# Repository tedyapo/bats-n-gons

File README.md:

# bats-n-gons
Nocturnal flying mammals, geometric shapes, and emergent behavior

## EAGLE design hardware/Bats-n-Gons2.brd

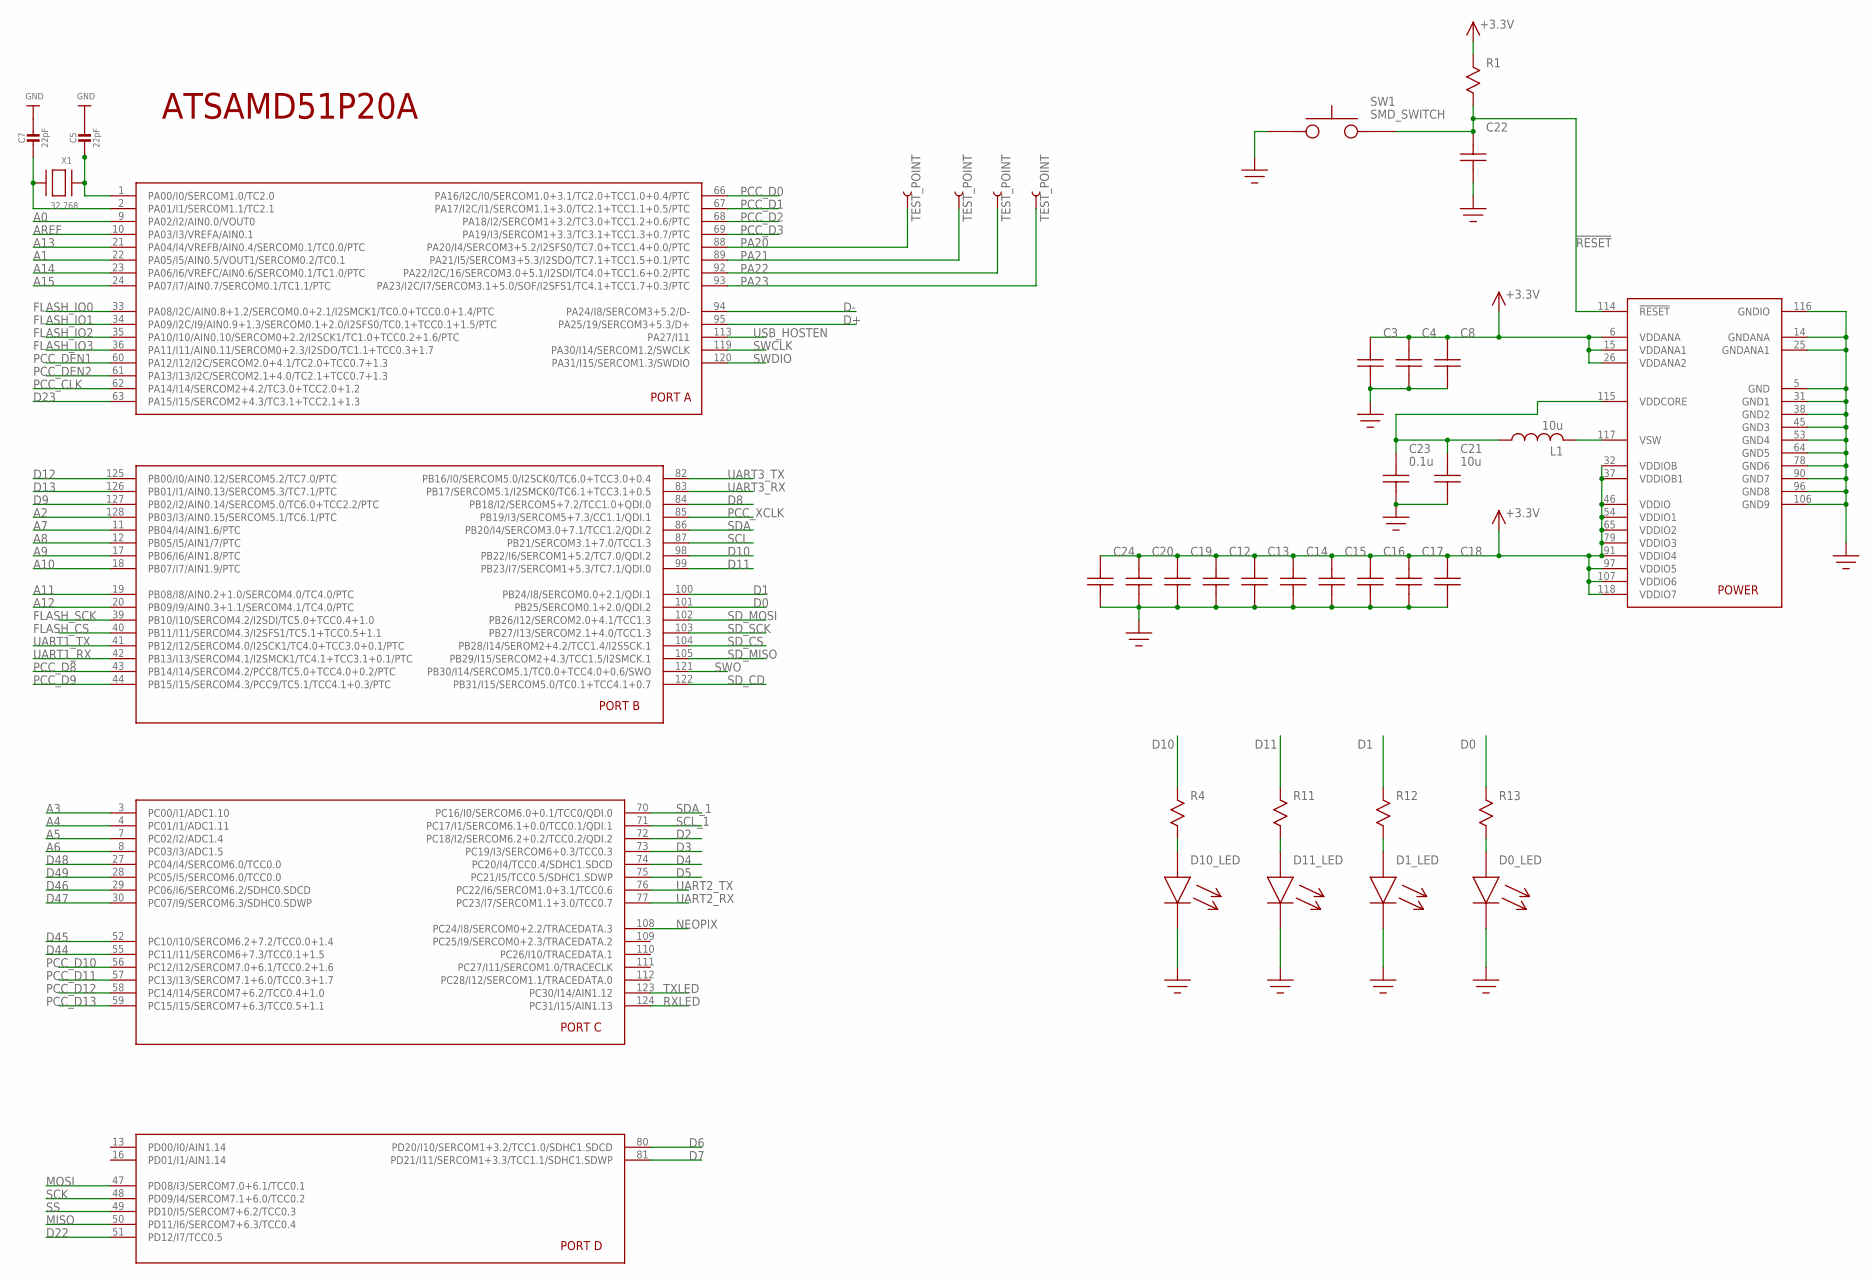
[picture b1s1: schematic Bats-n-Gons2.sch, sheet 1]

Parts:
C3, C4, C8, C12, C13, C14, C15, C16, C17, C18, C19, C20, C22, C24: C0603
C5, C7: 22pF; 0603-NO
C21: 10u; C0603
C23: 0.1u; C0603
D0_LED, D1_LED, D10_LED, D11_LED: LED_0603
L1: 10u; L24X24
R1, R4, R11, R12, R13: R0603
SW1: SMD_SWITCH
U1: SAMD51PXXA; SQFP-S-14X14-128
U$38, U$39, U$40, U$41: TEST_POINT; TEST_POINT_LARGE
X1: 32.768; XTAL3215

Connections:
!RESET!: C22.P$2, R1.P$2, SW1.P$3, SW1.P$4, U1.114 (!RESET); also elsewhere on the board
+3.3V: C3.P$2, C4.P$2, C8.P$2, C12.P$2, C13.P$2, C14.P$2, C15.P$2, C16.P$2, C17.P$2, C18.P$2, C19.P$2, C20.P$2, C24.P$2, R1.P$1, U1.6 (VDDANA), U1.15 (VDDANA1), U1.26 (VDDANA2), U1.32 (VDDIOB), U1.37 (VDDIOB1), U1.46 (VDDIO), U1.54 (VDDIO1), U1.65 (VDDIO2), U1.79 (VDDIO3), U1.91 (VDDIO4), U1.97 (VDDIO5), U1.107 (VDDIO6), U1.118 (VDDIO7); also elsewhere on the board
A0: U1.9 (PA02/I2/AIN0.0/VOUT0); also elsewhere on the board
A1: U1.22 (PA05/I5/AIN0.5/VOUT1/SERCOM0.2/TC0.1); also elsewhere on the board
A2: U1.128 (PB03/I3/AIN0.15/SERCOM5.1/TC6.1/PTC); also elsewhere on the board
A3: U1.3 (PC00/I1/ADC1.10)
A4: U1.4 (PC01/I1/ADC1.11)
A5: U1.7 (PC02/I2/ADC1.4)
A6: U1.8 (PC03/I3/ADC1.5)
A7: U1.11 (PB04/I4/AIN1.6/PTC)
A8: U1.12 (PB05/I5/AIN1/7/PTC)
A9: U1.17 (PB06/I6/AIN1.8/PTC)
A10: U1.18 (PB07/I7/AIN1.9/PTC)
A11: U1.19 (PB08/I8/AIN0.2+1.0/SERCOM4.0/TC4.0/PTC)
A12: U1.20 (PB09/I9/AIN0.3+1.1/SERCOM4.1/TC4.0/PTC)
A13: U1.21 (PA04/I4/VREFB/AIN0.4/SERCOM0.1/TC0.0/PTC)
A14: U1.23 (PA06/I6/VREFC/AIN0.6/SERCOM0.1/TC1.0/PTC)
A15: U1.24 (PA07/I7/AIN0.7/SERCOM0.1/TC1.1/PTC)
AREF: U1.10 (PA03/I3/VREFA/AIN0.1)
D0: R13.P$1, U1.101 (PB25/SERCOM0.1+2.0/QDI.2)
D1: R12.P$1, U1.100 (PB24/I8/SERCOM0.0+2.1/QDI.1)
D2: U1.72 (PC18/I2/SERCOM6.2+0.2/TCC0.2/QDI.2)
D3: U1.73 (PC19/I3/SERCOM6+0.3/TCC0.3)
D4: U1.74 (PC20/I4/TCC0.4/SDHC1.SDCD)
D5: U1.75 (PC21/I5/TCC0.5/SDHC1.SDWP)
D6: U1.80 (PD20/I10/SERCOM1+3.2/TCC1.0/SDHC1.SDCD)
D7: U1.81 (PD21/I11/SERCOM1+3.3/TCC1.1/SDHC1.SDWP)
D8: U1.84 (PB18/I2/SERCOM5+7.2/TCC1.0+QDI.0)
D9: U1.127 (PB02/I2/AIN0.14/SERCOM5.0/TC6.0+TCC2.2/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)
D10: R4.P$1, U1.98 (PB22/I6/SERCOM1+5.2/TC7.0/QDI.2)
D11: R11.P$1, U1.99 (PB23/I7/SERCOM1+5.3/TC7.1/QDI.0)
D12: U1.125 (PB00/I0/AIN0.12/SERCOM5.2/TC7.0/PTC)
D13: U1.126 (PB01/I1/AIN0.13/SERCOM5.3/TC7.1/PTC); also elsewhere on the board
D22: U1.51 (PD12/I7/TCC0.5)
D23: U1.63 (PA15/I15/SERCOM2+4.3/TC3.1+TCC2.1+1.3)
D44: U1.55 (PC11/I11/SERCOM6+7.3/TCC0.1+1.5)
D45: U1.52 (PC10/I10/SERCOM6.2+7.2/TCC0.0+1.4)
D46: U1.29 (PC06/I6/SERCOM6.2/SDHC0.SDCD); also elsewhere on the board
D47: U1.30 (PC07/I9/SERCOM6.3/SDHC0.SDWP)
D48: U1.27 (PC04/I4/SERCOM6.0/TCC0.0)
D49: U1.28 (PC05/I5/SERCOM6.0/TCC0.0)
D+: U1.95 (PA25/19/SERCOM3+5.3/D+); also elsewhere on the board
D-: U1.94 (PA24/I8/SERCOM3+5.2/D-); also elsewhere on the board
FLASH_CS: U1.40 (PB11/I11/SERCOM4.3/I2SFS1/TC5.1+TCC0.5+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)
FLASH_IO0: U1.33 (PA08/I2C/AIN0.8+1.2/SERCOM0.0+2.1/I2SMC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)
FLASH_IO1: U1.34 (PA09/I2C/I9/AIN0.9+1.3/SERCOM0.1+2.0/I2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)
FLASH_IO2: U1.35 (PA10/I10/AIN0.10/SERCOM0+2.2/I2SCK1/TC1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)
FLASH_IO3: U1.36 (PA11/I11/AIN0.11/SERCOM0+2.3/I2SDO/TC1.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)
FLASH_SCK: U1.39 (PB10/I10/SERCOM4.2/I2SDI/TC5.0+TCC0.4+1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)
GND: C3.P$1, C4.P$1, C5.2, C7.2, C8.P$1, C12.P$1, C13.P$1, C14.P$1, C15.P$1, C16.P$1, C17.P$1, C18.P$1, C19.P$1, C20.P$1, C21.P$1, C22.P$1, C23.P$1, C24.P$1, D0_LED.C, D1_LED.C, D10_LED.C, D11_LED.C, SW1.P$1, SW1.P$2, U1.5 (GND), U1.14 (GNDANA), U1.25 (GNDANA1), U1.31 (GND1), U1.38 (GND2), U1.45 (GND3), U1.53 (GND4), U1.64 (GND5), U1.78 (GND6), U1.90 (GND7), U1.96 (GND8), U1.106 (GND9), U1.116 (GNDIO); also elsewhere on the board
MISO: U1.50 (PD11/I6/SERCOM7+6.3/TCC0.4)
MOSI: U1.47 (PD08/I3/SERCOM7.0+6.1/TCC0.1)
unnamed: C5.1, U1.1 (PA00/I0/SERCOM1.0/TC2.0), X1.P$1
unnamed: C7.1, U1.2 (PA01/I1/SERCOM1.1/TC2.1), X1.P$2
unnamed: C21.P$2, C23.P$2, L1.1, U1.115 (VDDCORE)
unnamed: L1.2, U1.117 (VSW)
unnamed: D10_LED.A, R4.P$2
unnamed: D11_LED.A, R11.P$2
unnamed: D1_LED.A, R12.P$2
unnamed: D0_LED.A, R13.P$2
NEOPIX: U1.108 (PC24/I8/SERCOM0+2.2/TRACEDATA.3); also elsewhere on the board
PA20: U1.88 (PA20/I4/SERCOM3+5.2/I2SFS0/TC7.0+TCC1.4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), U$38.P$1
PA21: U1.89 (PA21/I5/SERCOM3+5.3/I2SDO/TC7.1+TCC1.5+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), U$39.P$1
PA22: U1.92 (PA22/I2C/16/SERCOM3.0+5.1/I2SDI/TC4.0+T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), U$40.P$1
PA23: U1.93 (PA23/I2C/I7/SERCOM3.1+5.0/SOF/I2SFS1/TC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), U$41.P$1
PCC_CLK: U1.62 (PA14/I14/SERCOM2+4.2/TC3.0+TCC2.0+1.2)
PCC_D0: U1.66 (PA16/I2C/I0/SERCOM1.0+3.1/TC2.0+TCC1.0+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)
PCC_D1: U1.67 (PA17/I2C/I1/SERCOM1.1+3.0/TC2.1+TCC1.1+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)
PCC_D2: U1.68 (PA18/I2/SERCOM1+3.2/TC3.0+TCC1.2+0.6/PTC)
PCC_D3: U1.69 (PA19/I3/SERCOM1+3.3/TC3.1+TCC1.3+0.7/PTC)
PCC_D8: U1.43 (PB14/I14/SERCOM4.2/PCC8/TC5.0+TCC4.0+0.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)
PCC_D9: U1.44 (PB15/I15/SERCOM4.3/PCC9/TC5.1/TCC4.1+0.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)
PCC_D10: U1.56 (PC12/I12/SERCOM7.0+6.1/TCC0.2+1.6)
PCC_D11: U1.57 (PC13/I13/SERCOM7.1+6.0/TCC0.3+1.7)
PCC_D12: U1.58 (PC14/I14/SERCOM7+6.2/TCC0.4+1.0)
PCC_D13: U1.59 (PC15/I15/SERCOM7+6.3/TCC0.5+1.1)
PCC_DEN1: U1.60 (PA12/I12/I2C/SERCOM2.0+4.1/TC2.0+TCC0.7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)
PCC_DEN2: U1.61 (PA13/I13/I2C/SERCOM2.1+4.0/TC2.1+TCC0.7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)
PCC_XCLK: U1.85 (PB19/I3/SERCOM5+7.3/CC1.1/QDI.1)
RXLED: U1.124 (PC31/I15/AIN1.13); also elsewhere on the board
SCK: U1.48 (PD09/I4/SERCOM7.1+6.0/TCC0.2)
SCL: U1.87 (PB21/SERCOM3.1+7.0/TCC1.3)
SCL_1: U1.71 (PC17/I1/SERCOM6.1+0.0/TCC0.1/QDI.1)
SDA: U1.86 (PB20/I4/SERCOM3.0+7.1/TCC1.2/QDI.2)
SDA_1: U1.70 (PC16/I0/SERCOM6.0+0.1/TCC0/QDI.0)
SD_CD: U1.122 (PB31/I15/SERCOM5.0/TC0.1+TCC4.1+0.7)
SD_CS: U1.104 (PB28/I14/SEROM2+4.2/TCC1.4/I2SSCK.1)
SD_MISO: U1.105 (PB29/I15/SERCOM2+4.3/TCC1.5/I2SMCK.1)
SD_MOSI: U1.102 (PB26/I12/SERCOM2.0+4.1/TCC1.3)
SD_SCK: U1.103 (PB27/I13/SERCOM2.1+4.0/TCC1.3)
SS: U1.49 (PD10/I5/SERCOM7+6.2/TCC0.3)
SWCLK: U1.119 (PA30/I14/SERCOM1.2/SWCLK); also elsewhere on the board
SWDIO: U1.120 (PA31/I15/SERCOM1.3/SWDIO); also elsewhere on the board
SWO: U1.121 (PB30/I14/SERCOM5.1/TC0.0+TCC4.0+0.6/SWO)
TXLED: U1.123 (PC30/I14/AIN1.12); also elsewhere on the board
UART1_RX: U1.42 (PB13/I13/SERCOM4.1/I2SMCK1/TC4.1+TCC3.1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); also elsewhere on the board
UART1_TX: U1.41 (PB12/I12/SERCOM4.0/I2SCK1/TC4.0+TCC3.0+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); also elsewhere on the board
UART2_RX: U1.77 (PC23/I7/SERCOM1.1+3.0/TCC0.7)
UART2_TX: U1.76 (PC22/I6/SERCOM1.0+3.1/TCC0.6)
UART3_RX: U1.83 (PB17/SERCOM5.1/I2SMCK0/TC6.1+TCC3.1+0.5)
UART3_TX: U1.82 (PB16/I0/SERCOM5.0/I2SCK0/TC6.0+TCC3.0+0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)
USB_HOSTEN: U1.113 (PA27/I11)

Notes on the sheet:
ATSAMD51P20A

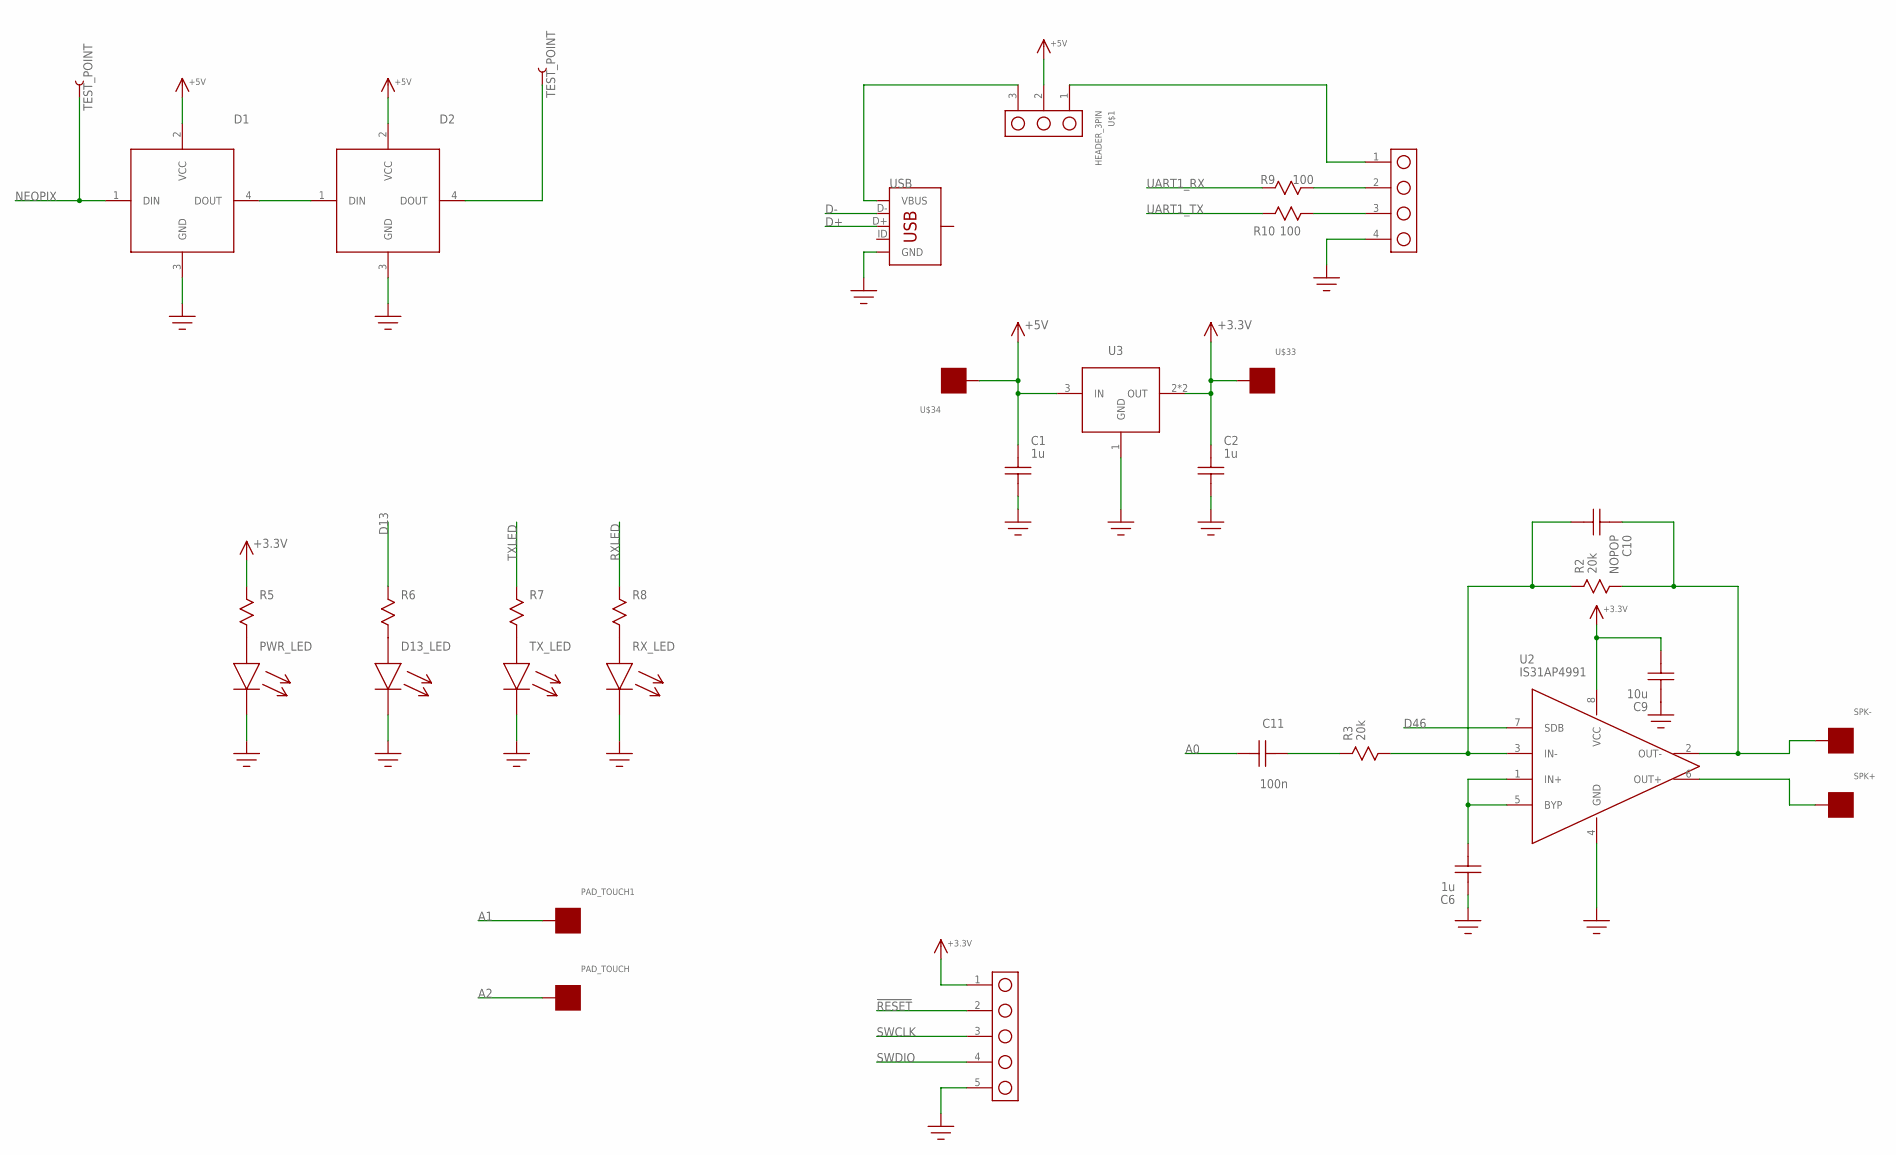
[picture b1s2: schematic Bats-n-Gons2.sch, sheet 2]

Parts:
C1, C2, C6: 1u; C0603
C9: 10u; 1206
C10: NOPOP; C0603
C11: 100n; C0603
D1, D2: NEOPIXEL; LED-RGB-THRU
D13_LED: LED_0603
DIN: TEST_POINT; TEST_POINT_LARGE
DOUT: TEST_POINT; TEST_POINT_LARGE
J1: HEADER_4PIN
J2: HEADER_5PIN
PAD_TOUCH, PAD_TOUCH1: PAD; PAD-ROUND-100MIL-MASK
PWR_LED: LED_0603
R2, R3: 20k; R0603
R5, R6, R7, R8: R0603
R9, R10: 100; R0603
RX_LED: LED_0603
SPK+: PAD100MIL; PAD_100MIL
SPK-: PAD100MIL; PAD_100MIL
TX_LED: LED_0603
U2: IS31AP4991; SOIC8
U3: AZ1117E; SOT-223
U$1: HEADER_3PIN
U$33, U$34: PADROUND-50MIL; PAD-ROUND-50MIL
USB: USB_MICRO_LEGS; USB_MICRO_LEGS_2

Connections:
!RESET!: J2.2; also elsewhere on the board
+3.3V: C2.P$2, C9.P$1, J2.1, R5.P$1, U2.8 (VCC), U3.2 (OUT), U3.4 (OUT), U$33.P$1; also elsewhere on the board
+5V: C1.P$2, D1.2 (VCC), D2.2 (VCC), U3.3 (IN), U$1.2, U$34.P$1
A0: C11.P$1; also elsewhere on the board
A1: PAD_TOUCH1.P$1; also elsewhere on the board
A2: PAD_TOUCH.P$1; also elsewhere on the board
D13: R6.P$1; also elsewhere on the board
D46: U2.7 (SDB); also elsewhere on the board
D+: USB.D+; also elsewhere on the board
D-: USB.D-; also elsewhere on the board
GND: C1.P$1, C2.P$1, C6.P$2, C9.P$2, D1.3 (GND), D2.3 (GND), D13_LED.C, J1.4, J2.5, PWR_LED.C, RX_LED.C, TX_LED.C, U2.4 (GND), U3.1 (GND), USB.GND; also elsewhere on the board
unnamed: C6.P$1, U2.1 (IN+), U2.5 (BYP)
unnamed: C10.P$2, R2.P$2, SPK-.P$1, U2.2 (OUT-)
unnamed: C10.P$1, R2.P$1, R3.P$2, U2.3 (IN-)
unnamed: C11.P$2, R3.P$1
unnamed: SPK+.P$1, U2.6 (OUT+)
unnamed: D2.4 (DOUT), DOUT.P$1
unnamed: J1.3, R10.P$2
unnamed: PWR_LED.A, R5.P$2
unnamed: D13_LED.A, R6.P$2
unnamed: R7.P$2, TX_LED.A
unnamed: R8.P$2, RX_LED.A
unnamed: J1.2, R9.P$2
unnamed: U$1.3, USB.VBUS
unnamed: J1.1, U$1.1
unnamed: D1.4 (DOUT), D2.1 (DIN)
NEOPIX: D1.1 (DIN), DIN.P$1; also elsewhere on the board
RXLED: R8.P$1; also elsewhere on the board
SWCLK: J2.3; also elsewhere on the board
SWDIO: J2.4; also elsewhere on the board
TXLED: R7.P$1; also elsewhere on the board
UART1_RX: R9.P$1; also elsewhere on the board
UART1_TX: R10.P$1; also elsewhere on the board

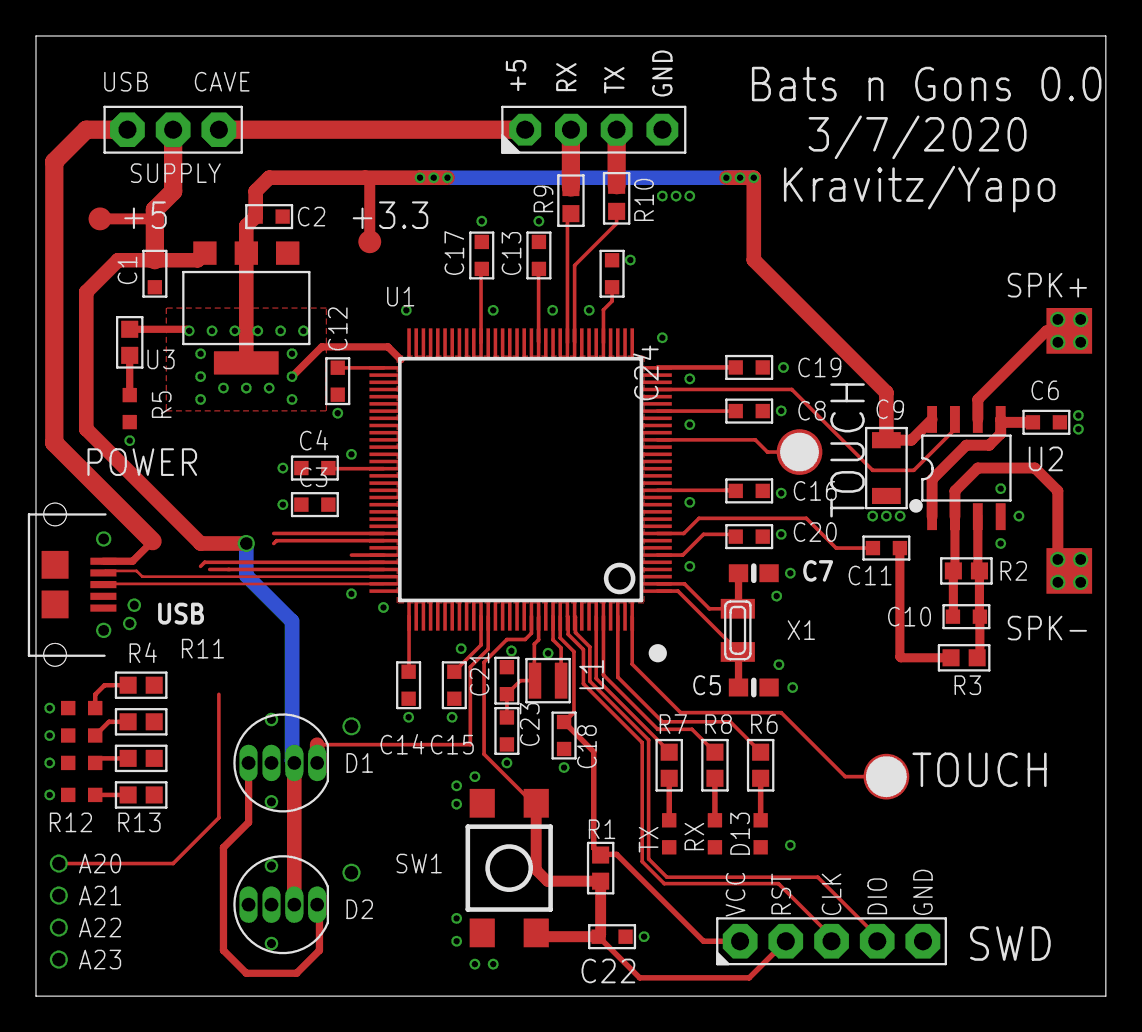
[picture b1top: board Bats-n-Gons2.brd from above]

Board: 2 copper layers, 59.4 x 53.3 mm, 69 parts (0 on the bottom side), 49 nets.

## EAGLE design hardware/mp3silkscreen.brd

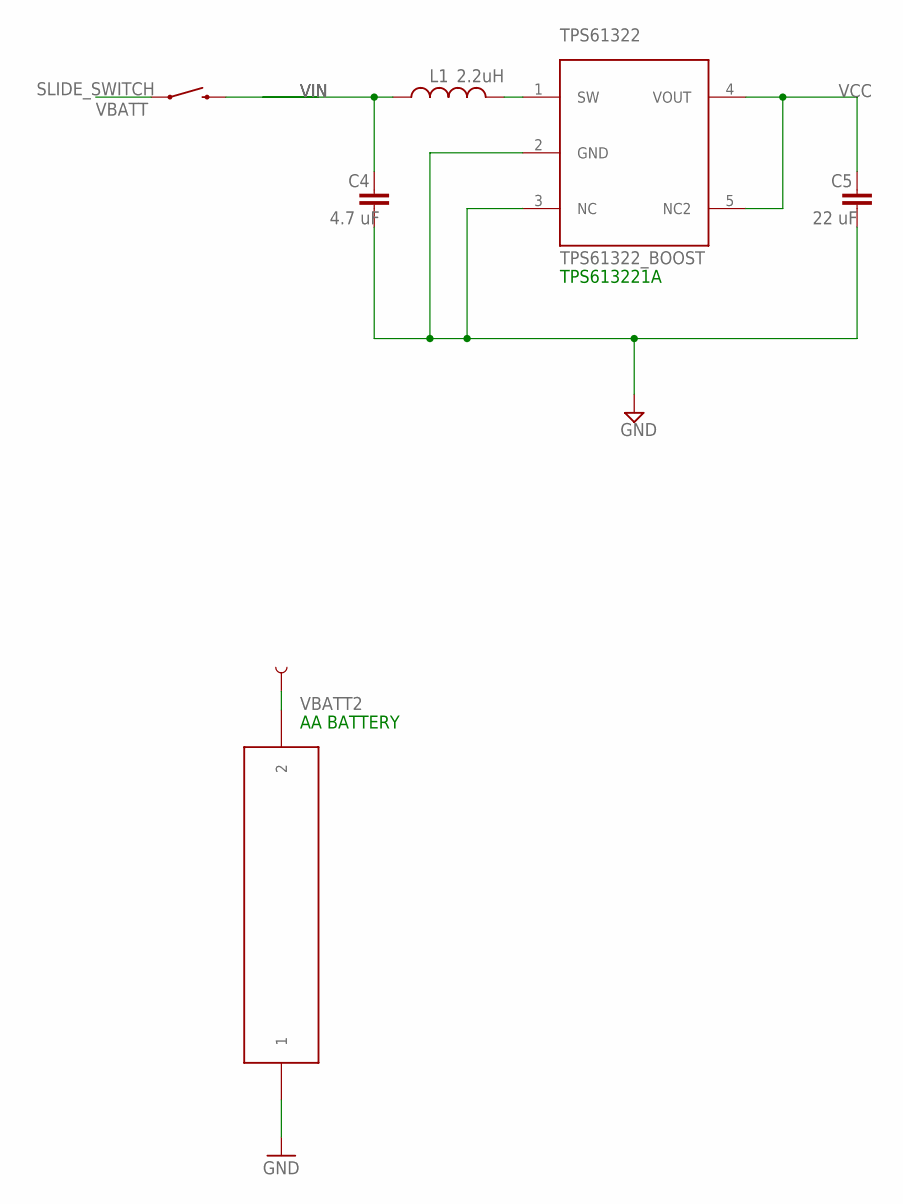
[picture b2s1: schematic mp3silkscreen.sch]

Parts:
C4: 4.7 uF; RESC0603_L
C5: 22 uF; RESC0603_L
L1: 2.2uH; RESC0805_L
TPS61322: TPS61322_BOOST; SOT23-5L
U$7: SLIDE_SWITCH
U$13: AA_BATT_HOLDER
U$15: TEST_POINT; TEST_POINT_LARGE

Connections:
GND: C4.2, C5.2, TPS61322.2 (GND), TPS61322.3 (NC), U$13.P$1 (1)
unnamed: L1.2, TPS61322.1 (SW)
VBATT: U$7.P$1 (1), U$7.P$2 (1)
VBATT2: U$13.P$2 (2), U$15.P$1
VCC: C5.1, TPS61322.4 (VOUT), TPS61322.5 (NC2)
VIN: C4.1, L1.1, U$7.P$3 (2)

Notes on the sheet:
TPS613221A
AA BATTERY

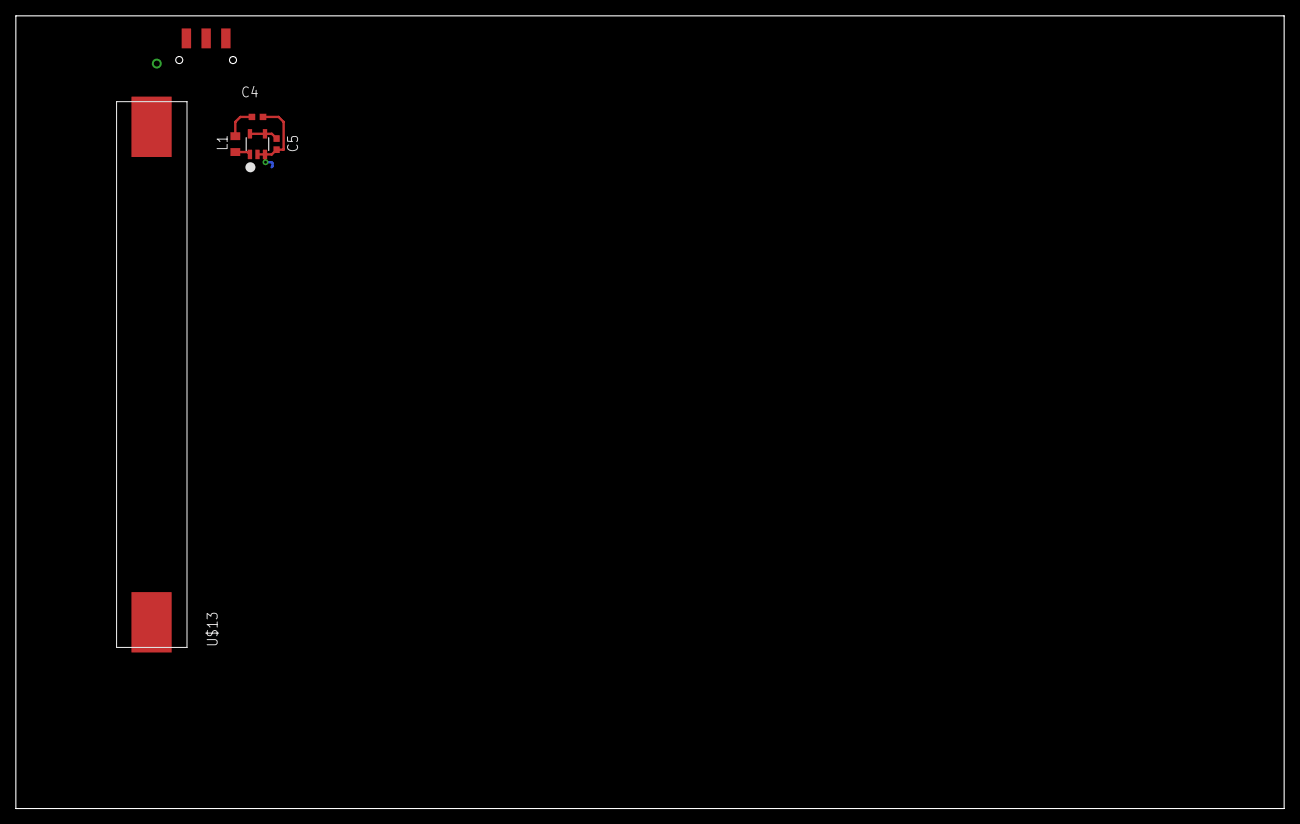
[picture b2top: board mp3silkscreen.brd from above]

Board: 2 copper layers, 160.0 x 100.0 mm, 7 parts (0 on the bottom side), 6 nets.

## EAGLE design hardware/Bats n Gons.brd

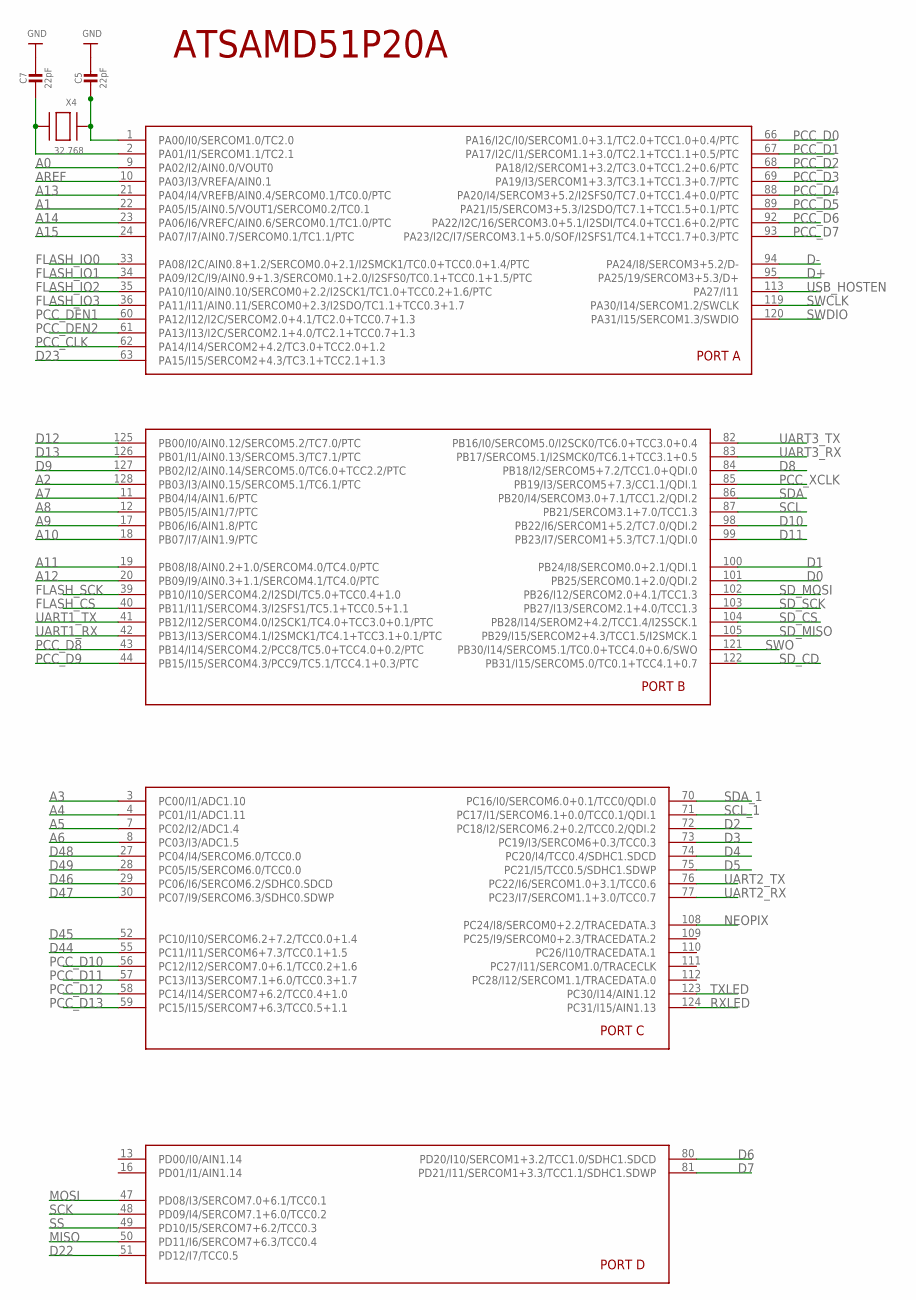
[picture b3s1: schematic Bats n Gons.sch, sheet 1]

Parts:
C5, C7: 22pF; 0603-NO
U$1: SAMD51PXXA; SQFP-S-14X14-128
X4: 32.768; XTAL3215

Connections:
A0: U$1.9 (PA02/I2/AIN0.0/VOUT0)
A1: U$1.22 (PA05/I5/AIN0.5/VOUT1/SERCOM0.2/TC0.1)
A2: U$1.128 (PB03/I3/AIN0.15/SERCOM5.1/TC6.1/PTC)
A3: U$1.3 (PC00/I1/ADC1.10)
A4: U$1.4 (PC01/I1/ADC1.11)
A5: U$1.7 (PC02/I2/ADC1.4)
A6: U$1.8 (PC03/I3/ADC1.5)
A7: U$1.11 (PB04/I4/AIN1.6/PTC)
A8: U$1.12 (PB05/I5/AIN1/7/PTC)
A9: U$1.17 (PB06/I6/AIN1.8/PTC)
A10: U$1.18 (PB07/I7/AIN1.9/PTC)
A11: U$1.19 (PB08/I8/AIN0.2+1.0/SERCOM4.0/TC4.0/PTC)
A12: U$1.20 (PB09/I9/AIN0.3+1.1/SERCOM4.1/TC4.0/PTC)
A13: U$1.21 (PA04/I4/VREFB/AIN0.4/SERCOM0.1/TC0.0/PTC)
A14: U$1.23 (PA06/I6/VREFC/AIN0.6/SERCOM0.1/TC1.0/PTC)
A15: U$1.24 (PA07/I7/AIN0.7/SERCOM0.1/TC1.1/PTC)
AREF: U$1.10 (PA03/I3/VREFA/AIN0.1)
D0: U$1.101 (PB25/SERCOM0.1+2.0/QDI.2)
D1: U$1.100 (PB24/I8/SERCOM0.0+2.1/QDI.1)
D2: U$1.72 (PC18/I2/SERCOM6.2+0.2/TCC0.2/QDI.2)
D3: U$1.73 (PC19/I3/SERCOM6+0.3/TCC0.3)
D4: U$1.74 (PC20/I4/TCC0.4/SDHC1.SDCD)
D5: U$1.75 (PC21/I5/TCC0.5/SDHC1.SDWP)
D6: U$1.80 (PD20/I10/SERCOM1+3.2/TCC1.0/SDHC1.SDCD)
D7: U$1.81 (PD21/I11/SERCOM1+3.3/TCC1.1/SDHC1.SDWP)
D8: U$1.84 (PB18/I2/SERCOM5+7.2/TCC1.0+QDI.0)
D9: U$1.127 (PB02/I2/AIN0.14/SERCOM5.0/TC6.0+TCC2.2/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)
D10: U$1.98 (PB22/I6/SERCOM1+5.2/TC7.0/QDI.2)
D11: U$1.99 (PB23/I7/SERCOM1+5.3/TC7.1/QDI.0)
D12: U$1.125 (PB00/I0/AIN0.12/SERCOM5.2/TC7.0/PTC)
D13: U$1.126 (PB01/I1/AIN0.13/SERCOM5.3/TC7.1/PTC)
D22: U$1.51 (PD12/I7/TCC0.5)
D23: U$1.63 (PA15/I15/SERCOM2+4.3/TC3.1+TCC2.1+1.3)
D44: U$1.55 (PC11/I11/SERCOM6+7.3/TCC0.1+1.5)
D45: U$1.52 (PC10/I10/SERCOM6.2+7.2/TCC0.0+1.4)
D46: U$1.29 (PC06/I6/SERCOM6.2/SDHC0.SDCD)
D47: U$1.30 (PC07/I9/SERCOM6.3/SDHC0.SDWP)
D48: U$1.27 (PC04/I4/SERCOM6.0/TCC0.0)
D49: U$1.28 (PC05/I5/SERCOM6.0/TCC0.0)
D+: U$1.95 (PA25/19/SERCOM3+5.3/D+)
D-: U$1.94 (PA24/I8/SERCOM3+5.2/D-)
FLASH_CS: U$1.40 (PB11/I11/SERCOM4.3/I2SFS1/TC5.1+TCC0.5+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)
FLASH_IO0: U$1.33 (PA08/I2C/AIN0.8+1.2/SERCOM0.0+2.1/I2SMC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)
FLASH_IO1: U$1.34 (PA09/I2C/I9/AIN0.9+1.3/SERCOM0.1+2.0/I2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)
FLASH_IO2: U$1.35 (PA10/I10/AIN0.10/SERCOM0+2.2/I2SCK1/TC1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)
FLASH_IO3: U$1.36 (PA11/I11/AIN0.11/SERCOM0+2.3/I2SDO/TC1.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)
FLASH_SCK: U$1.39 (PB10/I10/SERCOM4.2/I2SDI/TC5.0+TCC0.4+1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)
GND: C5.2, C7.2
MISO: U$1.50 (PD11/I6/SERCOM7+6.3/TCC0.4)
MOSI: U$1.47 (PD08/I3/SERCOM7.0+6.1/TCC0.1)
unnamed: C5.1, U$1.1 (PA00/I0/SERCOM1.0/TC2.0), X4.P$1
unnamed: C7.1, U$1.2 (PA01/I1/SERCOM1.1/TC2.1), X4.P$2
NEOPIX: U$1.108 (PC24/I8/SERCOM0+2.2/TRACEDATA.3)
PCC_CLK: U$1.62 (PA14/I14/SERCOM2+4.2/TC3.0+TCC2.0+1.2)
PCC_D0: U$1.66 (PA16/I2C/I0/SERCOM1.0+3.1/TC2.0+TCC1.0+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)
PCC_D1: U$1.67 (PA17/I2C/I1/SERCOM1.1+3.0/TC2.1+TCC1.1+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)
PCC_D2: U$1.68 (PA18/I2/SERCOM1+3.2/TC3.0+TCC1.2+0.6/PTC)
PCC_D3: U$1.69 (PA19/I3/SERCOM1+3.3/TC3.1+TCC1.3+0.7/PTC)
PCC_D4: U$1.88 (PA20/I4/SERCOM3+5.2/I2SFS0/TC7.0+TCC1.4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)
PCC_D5: U$1.89 (PA21/I5/SERCOM3+5.3/I2SDO/TC7.1+TCC1.5+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)
PCC_D6: U$1.92 (PA22/I2C/16/SERCOM3.0+5.1/I2SDI/TC4.0+T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)
PCC_D7: U$1.93 (PA23/I2C/I7/SERCOM3.1+5.0/SOF/I2SFS1/TC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)
PCC_D8: U$1.43 (PB14/I14/SERCOM4.2/PCC8/TC5.0+TCC4.0+0.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)
PCC_D9: U$1.44 (PB15/I15/SERCOM4.3/PCC9/TC5.1/TCC4.1+0.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)
PCC_D10: U$1.56 (PC12/I12/SERCOM7.0+6.1/TCC0.2+1.6)
PCC_D11: U$1.57 (PC13/I13/SERCOM7.1+6.0/TCC0.3+1.7)
PCC_D12: U$1.58 (PC14/I14/SERCOM7+6.2/TCC0.4+1.0)
PCC_D13: U$1.59 (PC15/I15/SERCOM7+6.3/TCC0.5+1.1)
PCC_DEN1: U$1.60 (PA12/I12/I2C/SERCOM2.0+4.1/TC2.0+TCC0.7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)
PCC_DEN2: U$1.61 (PA13/I13/I2C/SERCOM2.1+4.0/TC2.1+TCC0.7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)
PCC_XCLK: U$1.85 (PB19/I3/SERCOM5+7.3/CC1.1/QDI.1)
RXLED: U$1.124 (PC31/I15/AIN1.13)
SCK: U$1.48 (PD09/I4/SERCOM7.1+6.0/TCC0.2)
SCL: U$1.87 (PB21/SERCOM3.1+7.0/TCC1.3)
SCL_1: U$1.71 (PC17/I1/SERCOM6.1+0.0/TCC0.1/QDI.1)
SDA: U$1.86 (PB20/I4/SERCOM3.0+7.1/TCC1.2/QDI.2)
SDA_1: U$1.70 (PC16/I0/SERCOM6.0+0.1/TCC0/QDI.0)
SD_CD: U$1.122 (PB31/I15/SERCOM5.0/TC0.1+TCC4.1+0.7)
SD_CS: U$1.104 (PB28/I14/SEROM2+4.2/TCC1.4/I2SSCK.1)
SD_MISO: U$1.105 (PB29/I15/SERCOM2+4.3/TCC1.5/I2SMCK.1)
SD_MOSI: U$1.102 (PB26/I12/SERCOM2.0+4.1/TCC1.3)
SD_SCK: U$1.103 (PB27/I13/SERCOM2.1+4.0/TCC1.3)
SS: U$1.49 (PD10/I5/SERCOM7+6.2/TCC0.3)
SWCLK: U$1.119 (PA30/I14/SERCOM1.2/SWCLK)
SWDIO: U$1.120 (PA31/I15/SERCOM1.3/SWDIO)
SWO: U$1.121 (PB30/I14/SERCOM5.1/TC0.0+TCC4.0+0.6/SWO)
TXLED: U$1.123 (PC30/I14/AIN1.12)
UART1_RX: U$1.42 (PB13/I13/SERCOM4.1/I2SMCK1/TC4.1+TCC3.1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)
UART1_TX: U$1.41 (PB12/I12/SERCOM4.0/I2SCK1/TC4.0+TCC3.0+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)
UART2_RX: U$1.77 (PC23/I7/SERCOM1.1+3.0/TCC0.7)
UART2_TX: U$1.76 (PC22/I6/SERCOM1.0+3.1/TCC0.6)
UART3_RX: U$1.83 (PB17/SERCOM5.1/I2SMCK0/TC6.1+TCC3.1+0.5)
UART3_TX: U$1.82 (PB16/I0/SERCOM5.0/I2SCK0/TC6.0+TCC3.0+0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)
USB_HOSTEN: U$1.113 (PA27/I11)

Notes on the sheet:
ATSAMD51P20A

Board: 2 copper layers, 4 parts (0 on the bottom side), 3 nets, no tracks yet.

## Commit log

2020-03-04 first push
2020-03-05 silkscreen parts
2020-03-05 replaced spaces in file names with dashes added local library for components
2020-03-06 continued work on prototype board design
2020-03-07 checkpoint
2020-03-07 wheeeee
2020-03-08 maybe good enough for 0.0
2020-03-08 added SWD interface so we can actually install the bootloader :-)
2020-03-08 DRC checks out
2020-03-08 misc cleanup; added some ground pads
2020-03-08 file cleanup
2020-07-04 Integrated mouse-hat.dac
    Does not compile, added definitions to variables in IR_receiver.h

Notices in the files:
parts and their libraries:
microbuilder: This work is placed in the public domain, and may be freely used for commercial and non-commercial work with the following conditions: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
